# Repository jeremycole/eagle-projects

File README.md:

# Eagle projects by Jeremy Cole #

This is my working directories and projects built using [EAGLE](http://www.cadsoftusa.com/eagle-pcb-design-software/). 

# License #

These designs are copyright Jeremy Cole, but may be available for use. (Except for some files in "cam", and "dru" which relate to manufacture by third parties.) Please contact me at [jeremy@jcole.us](mailto:jeremy@jcole.us) if you're interested in selling, using, or repurposing my designs for anything.

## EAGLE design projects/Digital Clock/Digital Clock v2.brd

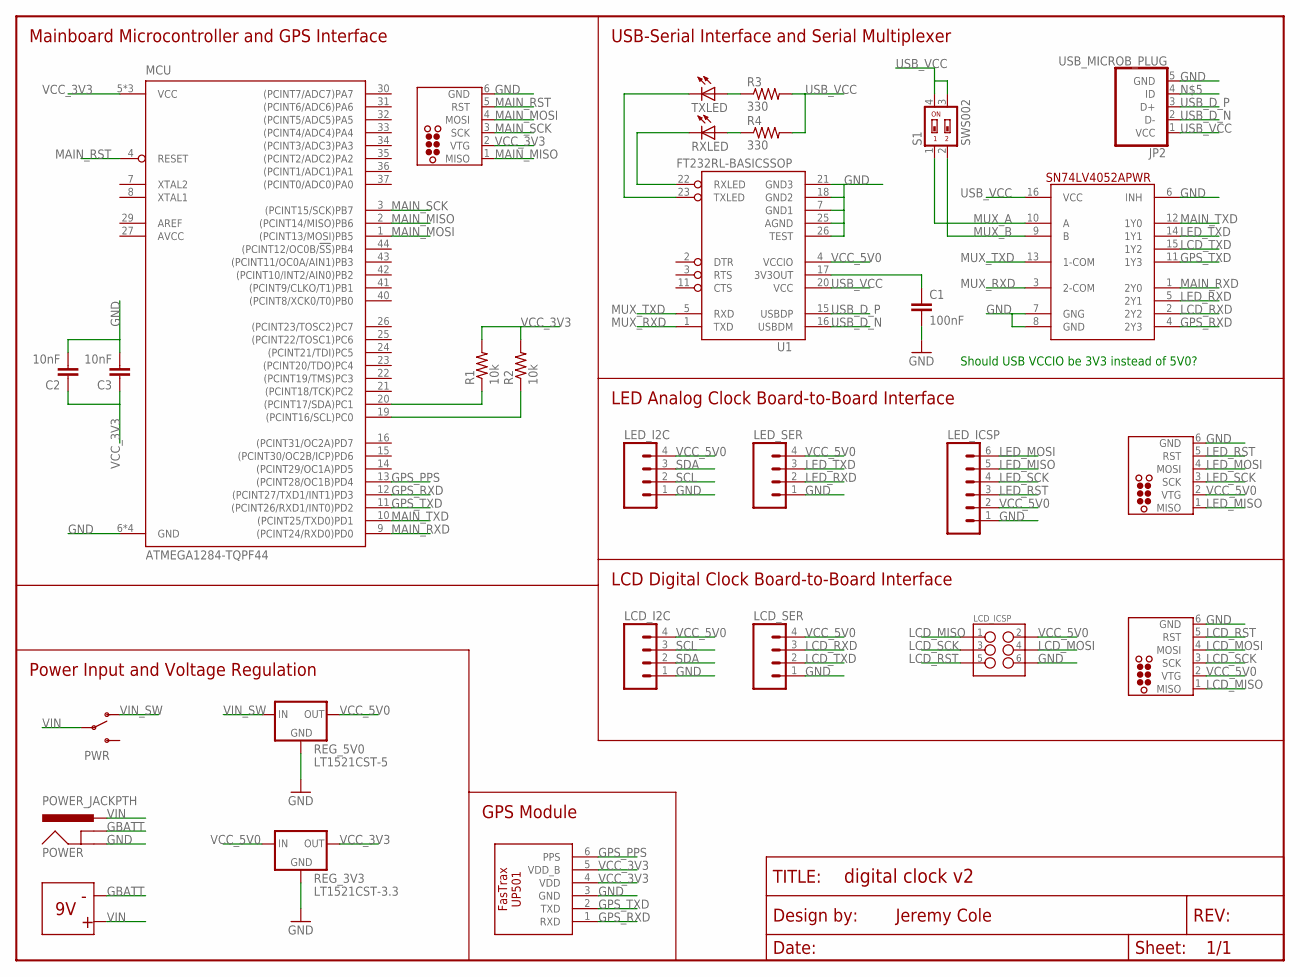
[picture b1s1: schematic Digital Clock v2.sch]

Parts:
9V_BATTERY: BATTERY-BH9VGLUE; BATTERY-BH9V-GLUE
C1: 100nF; 0603-CAP
C2, C3: 10nF; 0603-CAP
FRAME1: FRAME-LETTERNO_PACKAGE; DUMMY
GPS_ICSP_TC: TC2030-AVR-NL; TC2030-NL
JP2: USB_MICROB_PLUG; USB_MICRO_B_TYCO
LCD_I2C: M04LONGPADS; 1X04_LONGPADS
LCD_ICSP: M03X22X3_SILK_MALE_PTH; 2X3
LCD_ICSP_TC: TC2030-AVR-NL; TC2030-NL
LCD_SER: M04LONGPADS; 1X04_LONGPADS
LED_I2C: M04LONGPADS; 1X04_LONGPADS
LED_ICSP: M06LONGPADS; 1X06_LONGPADS
LED_ICSP_TC: TC2030-AVR-NL; TC2030-NL
LED_SER: M04LONGPADS; 1X04_LONGPADS
MCU: ATMEGA1284-TQPF44; TQFP44
POWER: POWER_JACKPTH; POWER_JACK_PTH
PWR: SWITCH-SPSTPTH; SWITCH-SPDT
R1, R2: 10k; 0603
R3, R4: 330; 0603
REG_3V3: LT1521CST-3.3; SOT223
REG_5V0: LT1521CST-5; SOT223
RXLED: LED-0603; 0603-LED
S1: SWS002; SMS-002
TXLED: LED-0603; 0603-LED
U1: FT232RL-BASICSSOP; SSOP28DB
U$15: FASTRAX-UP501
U$16: SV74LV4052APWR; TSSOP16

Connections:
AVCC: MCU.27 (AVCC)
GBATT: 9V_BATTERY.9V-, POWER.GNDBREAK
GND: C1.2, C2.2, C3.2, GPS_ICSP_TC.6 (GND), JP2.5 (GND), LCD_I2C.1, LCD_ICSP.6, LCD_ICSP_TC.6 (GND), LCD_SER.1, LED_I2C.1, LED_ICSP.1, LED_ICSP_TC.6 (GND), LED_SER.1, MCU.6 (GND), MCU.18 (GND), MCU.28 (GND), MCU.39 (GND), POWER.GND, REG_3V3.2 (GND), REG_3V3.TAB (GND), REG_5V0.2 (GND), REG_5V0.TAB (GND), U1.7 (GND1), U1.18 (GND2), U1.21 (GND3), U1.25 (AGND), U1.26 (TEST), U$15.3 (GND), U$16.6 (INH), U$16.7 (GNG), U$16.8 (GND)
GPS_PPS: MCU.13 ((PCINT28/OC1B)PD4), U$15.6 (PPS)
GPS_RXD: MCU.12 ((PCINT27/TXD1/INT1)PD3), U$15.1 (RXD), U$16.4 (2Y3)
GPS_TXD: MCU.11 ((PCINT26/RXD1/INT0)PD2), U$15.2 (TXD), U$16.11 (1Y3)
LCD_MISO: LCD_ICSP.1, LCD_ICSP_TC.1 (MISO)
LCD_MOSI: LCD_ICSP.4, LCD_ICSP_TC.4 (MOSI)
LCD_RST: LCD_ICSP.5, LCD_ICSP_TC.5 (RST)
LCD_RXD: LCD_SER.3, U$16.2 (2Y2)
LCD_SCK: LCD_ICSP.3, LCD_ICSP_TC.3 (SCK)
LCD_TXD: LCD_SER.2, U$16.15 (1Y2)
LED_MISO: LED_ICSP.5, LED_ICSP_TC.1 (MISO)
LED_MOSI: LED_ICSP.6, LED_ICSP_TC.4 (MOSI)
LED_RST: LED_ICSP.3, LED_ICSP_TC.5 (RST)
LED_RXD: LED_SER.2, U$16.5 (2Y1)
LED_SCK: LED_ICSP.4, LED_ICSP_TC.3 (SCK)
LED_TXD: LED_SER.3, U$16.14 (1Y1)
MAIN_MISO: GPS_ICSP_TC.1 (MISO), MCU.2 ((PCINT14/MISO)PB6)
MAIN_MOSI: GPS_ICSP_TC.4 (MOSI), MCU.1 ((PCINT13/MOSI)PB5)
MAIN_RST: GPS_ICSP_TC.5 (RST), MCU.4 (RESET)
MAIN_RXD: MCU.9 ((PCINT24/RXD0)PD0), U$16.1 (2Y0)
MAIN_SCK: GPS_ICSP_TC.3 (SCK), MCU.3 ((PCINT15/SCK)PB7)
MAIN_TXD: MCU.10 ((PCINT25/TXD0)PD1), U$16.12 (1Y0)
MUX_A: S1.1, U$16.10 (A)
MUX_B: S1.2, U$16.9 (B)
MUX_RXD: U1.1 (TXD), U$16.3 (2-COM)
MUX_TXD: U1.5 (RXD), U$16.13 (1-COM)
unnamed: R3.1, TXLED.A
unnamed: R4.1, RXLED.A
unnamed: C1.1, U1.17 (3V3OUT)
unnamed: TXLED.C, U1.23 (TXLED)
unnamed: RXLED.C, U1.22 (RXLED)
SCL: LCD_I2C.3, LED_I2C.2, MCU.19 ((PCINT16/SCL)PC0), R2.1
SDA: LCD_I2C.2, LED_I2C.3, MCU.20 ((PCINT17/SDA)PC1), R1.1
USB_D_N: JP2.2 (D-), U1.16 (USBDM)
USB_D_P: JP2.3 (D+), U1.15 (USBDP)
USB_VCC: JP2.1 (VCC), R3.2, R4.2, S1.3, S1.4, U1.20 (VCC), U$16.16 (VCC)
VCC_3V3: C2.1, C3.1, GPS_ICSP_TC.2 (VTG), MCU.5 (VCC), MCU.17 (VCC), MCU.38 (VCC), R1.2, R2.2, REG_3V3.3 (OUT), U$15.4 (VDD), U$15.5 (VDD_B)
VCC_5V0: LCD_I2C.4, LCD_ICSP.2, LCD_ICSP_TC.2 (VTG), LCD_SER.4, LED_I2C.4, LED_ICSP.2, LED_ICSP_TC.2 (VTG), LED_SER.4, REG_3V3.1 (IN), REG_5V0.3 (OUT), U1.4 (VCCIO)
VIN: 9V_BATTERY.9V+, POWER.PWR, PWR.2
VIN_SW: PWR.1 (O), REG_5V0.1 (IN)

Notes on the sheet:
Should USB VCCIO be 3V3 instead of 5V0?
Jeremy Cole
Power Input and Voltage Regulation
Mainboard Microcontroller and GPS Interface
USB-Serial Interface and Serial Multiplexer
LED Analog Clock Board-to-Board Interface
LCD Digital Clock Board-to-Board Interface
GPS Module

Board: 2 copper layers, 44 parts (16 on the bottom side), 41 nets, no tracks yet.

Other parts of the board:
U$1, U$2, U$3, U$4, U$5, U$6, U$7, U$8, U$9, U$10, U$11, U$12, U$13, U$14: STAND-OFF

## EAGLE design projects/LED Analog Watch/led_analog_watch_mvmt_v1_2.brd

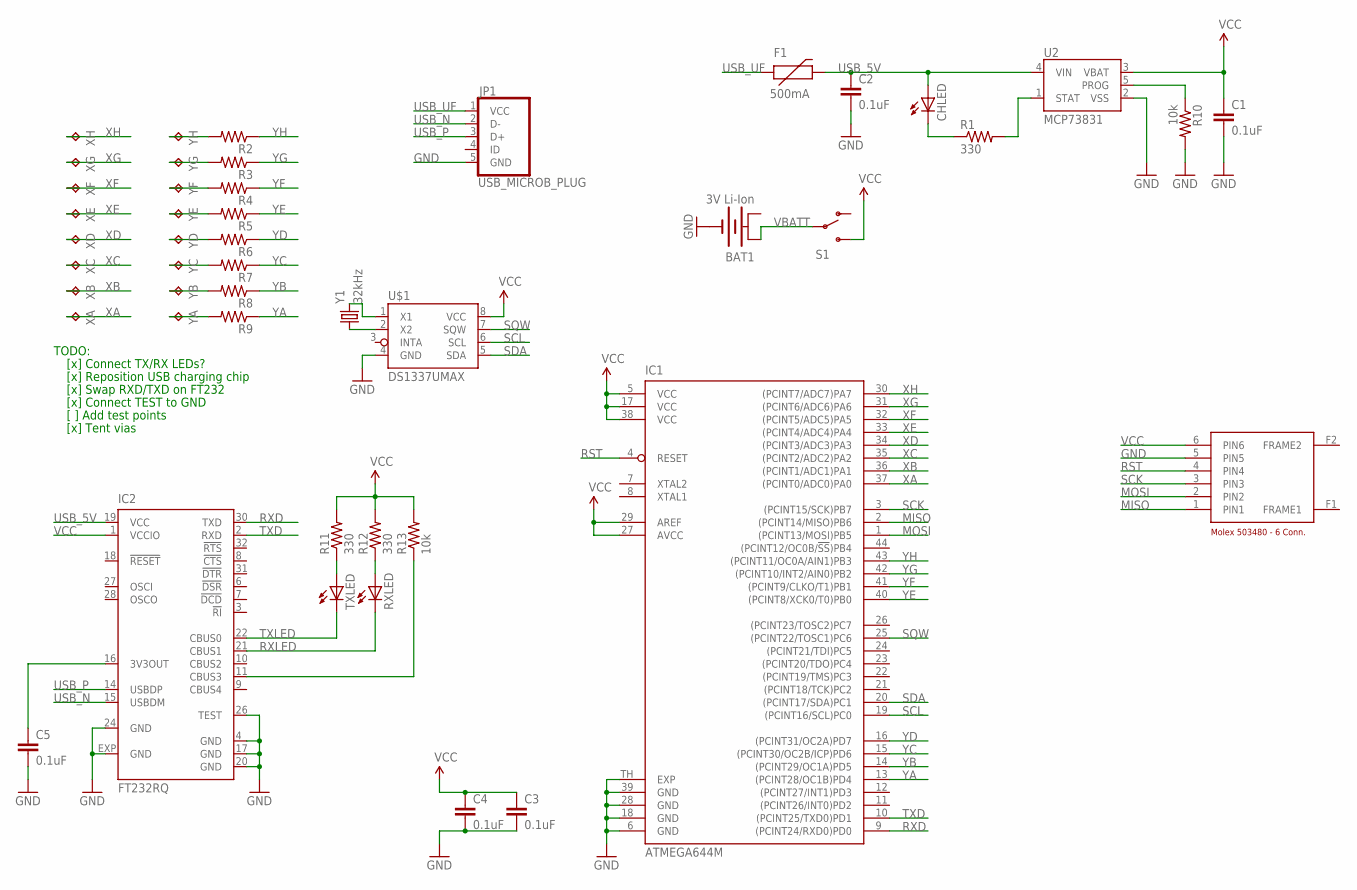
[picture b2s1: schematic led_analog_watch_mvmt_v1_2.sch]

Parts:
BAT1: 3V Li-Ion; BATTCON_245MM_PTH
C1, C2, C3, C4, C5: 0.1uF; 0603-CAP
CHLED: LED-0402; 0402
F1: 500mA; 0603
IC1: ATMEGA644M; MLF44-TH
IC2: FT232RQ; QFN32
JP1: USB_MICROB_PLUG; USB_MICRO_B_TYCO
R1, R11, R12: 330; 0603
R2, R3, R4, R5, R6, R7, R8, R9: RESISTOR-0603; 0603
R10, R13: 10k; 0603
RXLED: LED-0402; 0402
S1: SWITCH-SPSTMA12R; SWITCH-MA12R
TXLED: LED-0402; 0402
U2: MCP73831; SOT23-5
U$1: DS1337UMAX; UMAX8
U$2: MOLEX_503480
XA: TPTP20R; TP20R
XB: TPTP20R; TP20R
XC: TPTP20R; TP20R
XD: TPTP20R; TP20R
XE: TPTP20R; TP20R
XF: TPTP20R; TP20R
XG: TPTP20R; TP20R
XH: TPTP20R; TP20R
Y1: 32kHz; CRYSTAL-ABS10-SMD
YA: TPTP20R; TP20R
YB: TPTP20R; TP20R
YC: TPTP20R; TP20R
YD: TPTP20R; TP20R
YE: TPTP20R; TP20R
YF: TPTP20R; TP20R
YG: TPTP20R; TP20R
YH: TPTP20R; TP20R

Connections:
+B: BAT1.1 (+B)
GND: BAT1.2 (-), C1.2, C2.2, C3.2, C4.2, C5.2, IC1.6 (GND), IC1.18 (GND), IC1.28 (GND), IC1.39 (GND), IC1.TH (EXP), IC2.4 (GND), IC2.17 (GND), IC2.20 (GND), IC2.24 (GND), IC2.26 (TEST), IC2.EXP (GND), JP1.5 (GND), R10.2, U2.2 (VSS), U$1.4 (GND), U$2.5 (PIN5)
MISO: IC1.2 ((PCINT14/MISO)PB6), U$2.1 (PIN1)
MOSI: IC1.1 ((PCINT13/MOSI)PB5), U$2.2 (PIN2)
unnamed: R1.2, U2.1 (STAT)
unnamed: R10.1, U2.5 (PROG)
unnamed: R2.2, YH.TP
unnamed: R3.2, YG.TP
unnamed: R4.2, YF.TP
unnamed: R5.2, YE.TP
unnamed: R6.2, YD.TP
unnamed: R7.2, YC.TP
unnamed: R8.2, YB.TP
unnamed: R9.2, YA.TP
unnamed: CHLED.2 (C), R1.1
unnamed: IC2.11 (CBUS3), R13.1
unnamed: R12.1, RXLED.1 (A)
unnamed: U$1.2 (X2), Y1.X1 (1)
unnamed: U$1.1 (X1), Y1.X2 (2)
unnamed: R11.1, TXLED.1 (A)
unnamed: C5.1, IC2.16 (3V3OUT)
RST: IC1.4 (RESET), U$2.4 (PIN4)
RXD: IC1.9 ((PCINT24/RXD0)PD0), IC2.30 (TXD)
RXLED: IC2.21 (CBUS1), RXLED.2 (C)
SCK: IC1.3 ((PCINT15/SCK)PB7), U$2.3 (PIN3)
SCL: IC1.19 ((PCINT16/SCL)PC0), U$1.6 (SCL)
SDA: IC1.20 ((PCINT17/SDA)PC1), U$1.5 (SDA)
SQW: IC1.25 ((PCINT22/TOSC1)PC6), U$1.7 (SQW)
TXD: IC1.10 ((PCINT25/TXD0)PD1), IC2.2 (RXD)
TXLED: IC2.22 (CBUS0), TXLED.2 (C)
USB_5V: C2.1, CHLED.1 (A), F1.2, IC2.19 (VCC), U2.4 (VIN)
USB_N: IC2.15 (USBDM), JP1.2 (D-)
USB_P: IC2.14 (USBDP), JP1.3 (D+)
USB_UF: F1.1, JP1.1 (VCC)
VBATT: BAT1.3 (+A), S1.2
VCC: C1.1, C3.1, C4.1, IC1.5 (VCC), IC1.17 (VCC), IC1.27 (AVCC), IC1.29 (AREF), IC1.38 (VCC), IC2.1 (VCCIO), R11.2, R12.2, R13.2, S1.3 (S), U2.3 (VBAT), U$1.8 (VCC), U$2.6 (PIN6)
XA: IC1.37 ((PCINT0/ADC0)PA0), XA.TP
XB: IC1.36 ((PCINT1/ADC1)PA1), XB.TP
XC: IC1.35 ((PCINT2/ADC2)PA2), XC.TP
XD: IC1.34 ((PCINT3/ADC3)PA3), XD.TP
XE: IC1.33 ((PCINT4/ADC4)PA4), XE.TP
XF: IC1.32 ((PCINT5/ADC5)PA5), XF.TP
XG: IC1.31 ((PCINT6/ADC6)PA6), XG.TP
XH: IC1.30 ((PCINT7/ADC7)PA7), XH.TP
YA: IC1.13 ((PCINT28/OC1B)PD4), R9.1
YB: IC1.14 ((PCINT29/OC1A)PD5), R8.1
YC: IC1.15 ((PCINT30/OC2B/ICP)PD6), R7.1
YD: IC1.16 ((PCINT31/OC2A)PD7), R6.1
YE: IC1.40 ((PCINT8/XCK0/T0)PB0), R5.1
YF: IC1.41 ((PCINT9/CLKO/T1)PB1), R4.1
YG: IC1.42 ((PCINT10/INT2/AIN0)PB2), R3.1
YH: IC1.43 ((PCINT11/OC0A/AIN1)PB3), R2.1

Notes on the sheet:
TODO:
[x] Connect TX/RX LEDs?
[x] Reposition USB charging chip
[x] Swap RXD/TXD on FT232
[x] Connect TEST to GND
[ ] Add test points
[x] Tent vias

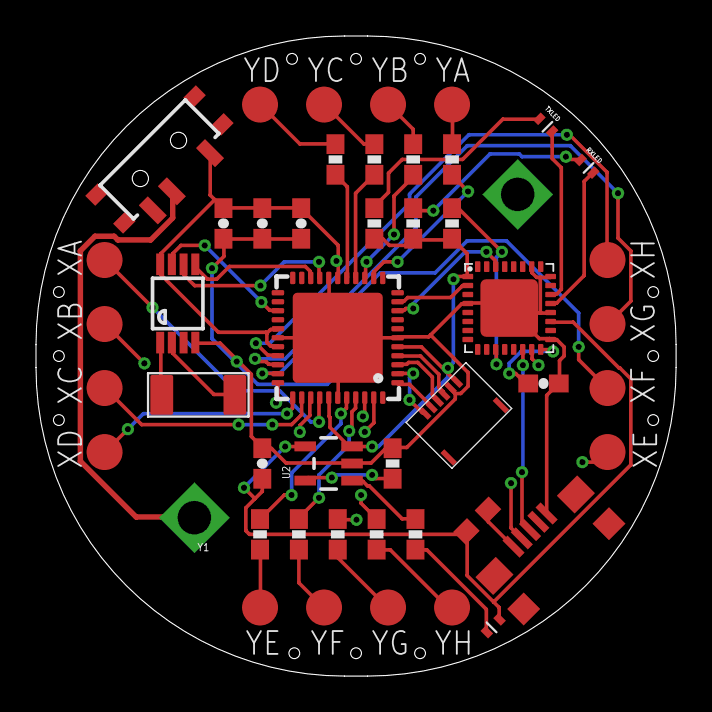
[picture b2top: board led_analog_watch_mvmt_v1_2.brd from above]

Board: 4 copper layers, 35.6 x 35.6 mm, 47 parts (1 on the bottom side), 51 nets.

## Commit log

2012-03-19 Initial checkin
2012-03-22 Rename ffc adapter files
2012-03-22 Remove marker dot that violates design constraints
2012-03-22 Correct silkscreen text
2012-04-28 Add initial .gitignore
2012-04-28 Add 4-layer SFE Gerber CAM job
2012-05-05 Housekeeping on lbr and add dru and cam jobs for Laen's PCB fab
2012-05-05 Add all the output formats for cam jobs to .gitignore
2012-05-05 Add README
2012-05-06 Add DESCRIPTION files for my directories
2012-05-06 Minor adjustments to watch movement; Auto-routing; Export CAM for Laen fabrication
2012-05-06 Adjust symbol for FFC connector on schematic
2012-05-07 Update library parts adding ATmega644PA in TQFP44
2012-05-07 Initial revision of Digital Clock v2
2012-05-07 Initial revision of GPS I2C interface
2012-05-28 Rename LaenPCBOrder.dru to -4layer to allow for getting back a 2-layer version
2012-05-28 Tent vias
2012-05-28 Add original 2-layer version of Laen's DRU
2012-05-28 Add version 2 of LED Analog Watch Movement, correcting several errors
2012-05-28 Add version 1.2 of LED Analog Watch Movement, correcting several errors
2012-05-28 Rename layer02 -> internalplane1, layer15 -> internalplane2 in Lane 4-layer CAM
2012-07-02 Minor adjustments to schematic and docs
2012-07-02 Version 1.3 of LED Analog Watch
2015-11-30 Add new parts to library
2015-11-30 Add OSHPark CAM files
2015-11-30 Add TagConnect lbr
2015-11-30 Add new Digital Clock v2 design, update eagle.epf
2015-12-07 Many minor revisions to Digital Clock v2

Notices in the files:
projects/Digital Clock/Digital Clock v2.brd:
(c) 2015 Jeremy Cole
parts and their libraries:
jcole: ©2009 ROFA.cz - modified and updated by Robert Darlington ‹rdarlington@gmail.com›
SparkFun-Connectors: Licensing: Creative Commons ShareAlike 4.0 International - https://creativecommons.org/licenses/by-sa/4.0
jcole: Released under the Creative Commons Attribution Share-Alike 4.0 License
